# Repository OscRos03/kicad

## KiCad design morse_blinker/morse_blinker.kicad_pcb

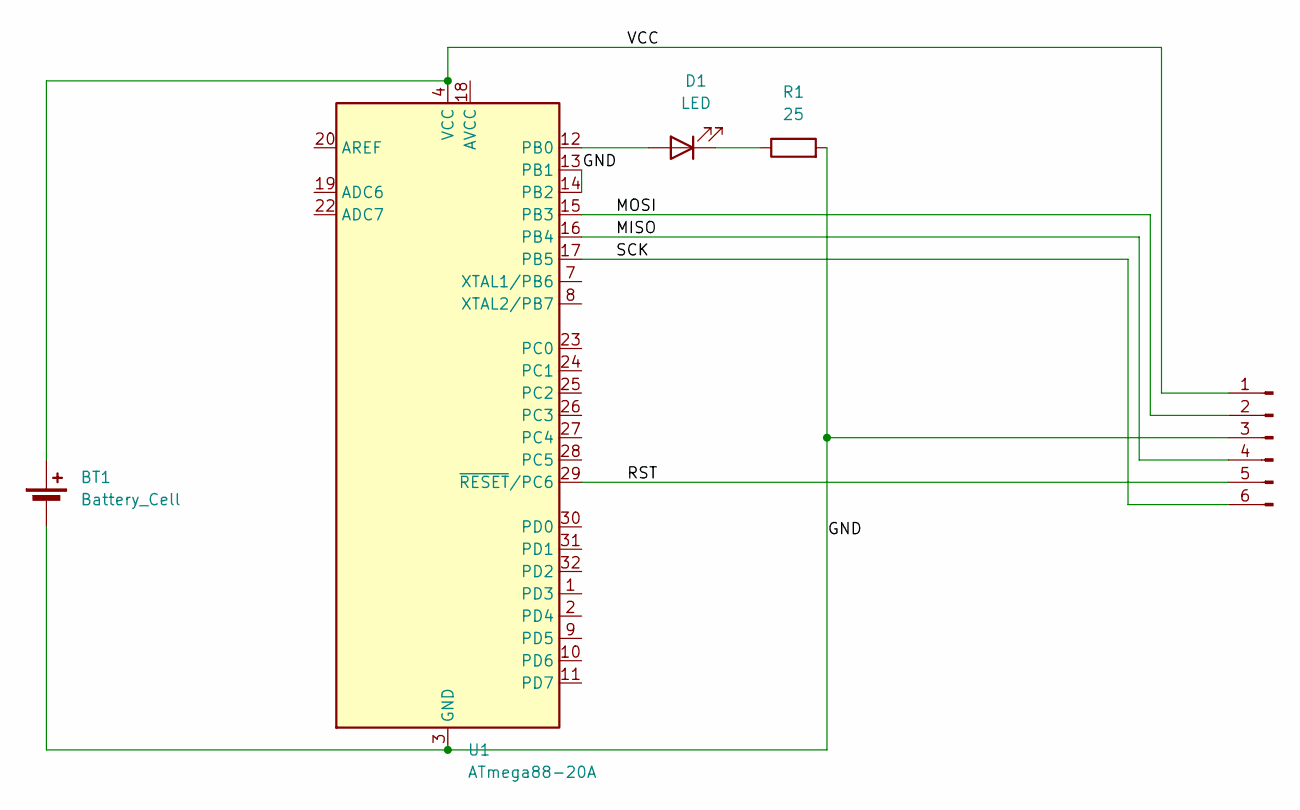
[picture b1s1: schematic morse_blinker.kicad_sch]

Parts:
BT1: Battery_Cell; BAT_106
D1: LED; LED_0805_2012Metric
J1: Conn_01x06_Pin; Tag-Connect_TC2030-IDC-NL_2x03_P1.27mm_Vertical
R1: 25; R_0603_1608Metric_Pad0.98x0.95mm_HandSolder
U1: ATmega88-20A; TQFP-32_7x7mm_P0.8mm

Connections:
/GND: BT1.2 (-), J1.3, R1.2, U1.3 (GND), U1.5 (GND), U1.13 (PB1), U1.14 (PB2), U1.21 (GND)
/MISO: J1.4, U1.16 (PB4)
/MOSI: J1.2, U1.15 (PB3)
/RST: J1.5, U1.29 (~RESET/PC6)
/SCK: J1.6, U1.17 (PB5)
/VCC: BT1.1 (+), J1.1, U1.4 (VCC), U1.6 (VCC)
unnamed: D1.2 (A), U1.12 (PB0)
unnamed: D1.1 (K), R1.1

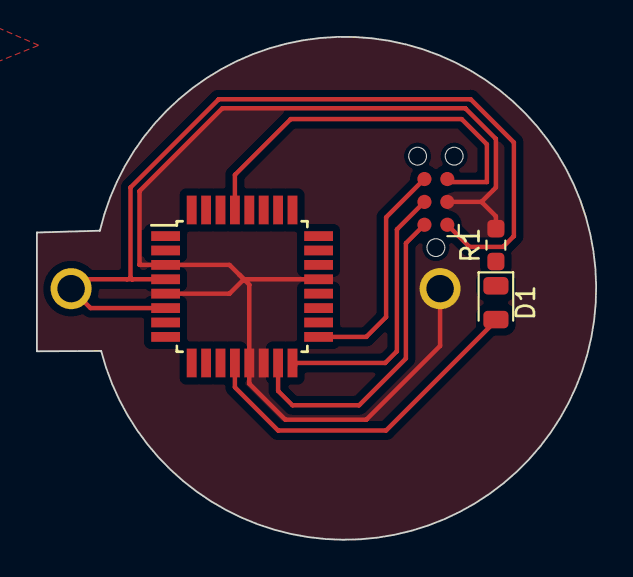
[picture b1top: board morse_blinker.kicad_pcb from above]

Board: 2 copper layers, 31.1 x 27.9 mm, 5 parts (1 on the bottom side), 8 nets.

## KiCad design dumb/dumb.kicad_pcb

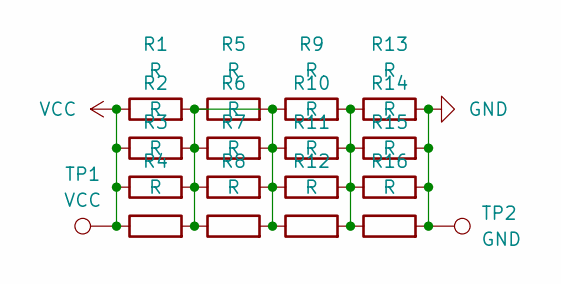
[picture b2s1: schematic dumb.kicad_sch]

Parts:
R1, R2, R3, R4, R5, R6, R7, R8, R9, R10, R11, R12, R13, R14, R15, R16: R; R_01005_0402Metric
TP1: VCC; TestPoint_Pad_1.0x1.0mm
TP2: GND; TestPoint_Pad_1.0x1.0mm

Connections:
GND: R13.2, R14.2, R15.2, R16.2, TP2.1
unnamed: R1.2, R2.2, R3.2, R4.2, R5.1, R6.1, R7.1, R8.1
unnamed: R5.2, R6.2, R7.2, R8.2, R9.1, R10.1, R11.1, R12.1
unnamed: R9.2, R10.2, R11.2, R12.2, R13.1, R14.1, R15.1, R16.1
VCC: R1.1, R2.1, R3.1, R4.1, TP1.1

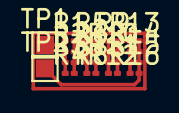
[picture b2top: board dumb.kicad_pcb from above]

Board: 2 copper layers, 18 parts (0 on the bottom side), 5 nets.

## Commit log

2023-11-09 inital commit
2024-01-17 giga commit
2024-01-17 new symbols
2024-02-29 huge cock
